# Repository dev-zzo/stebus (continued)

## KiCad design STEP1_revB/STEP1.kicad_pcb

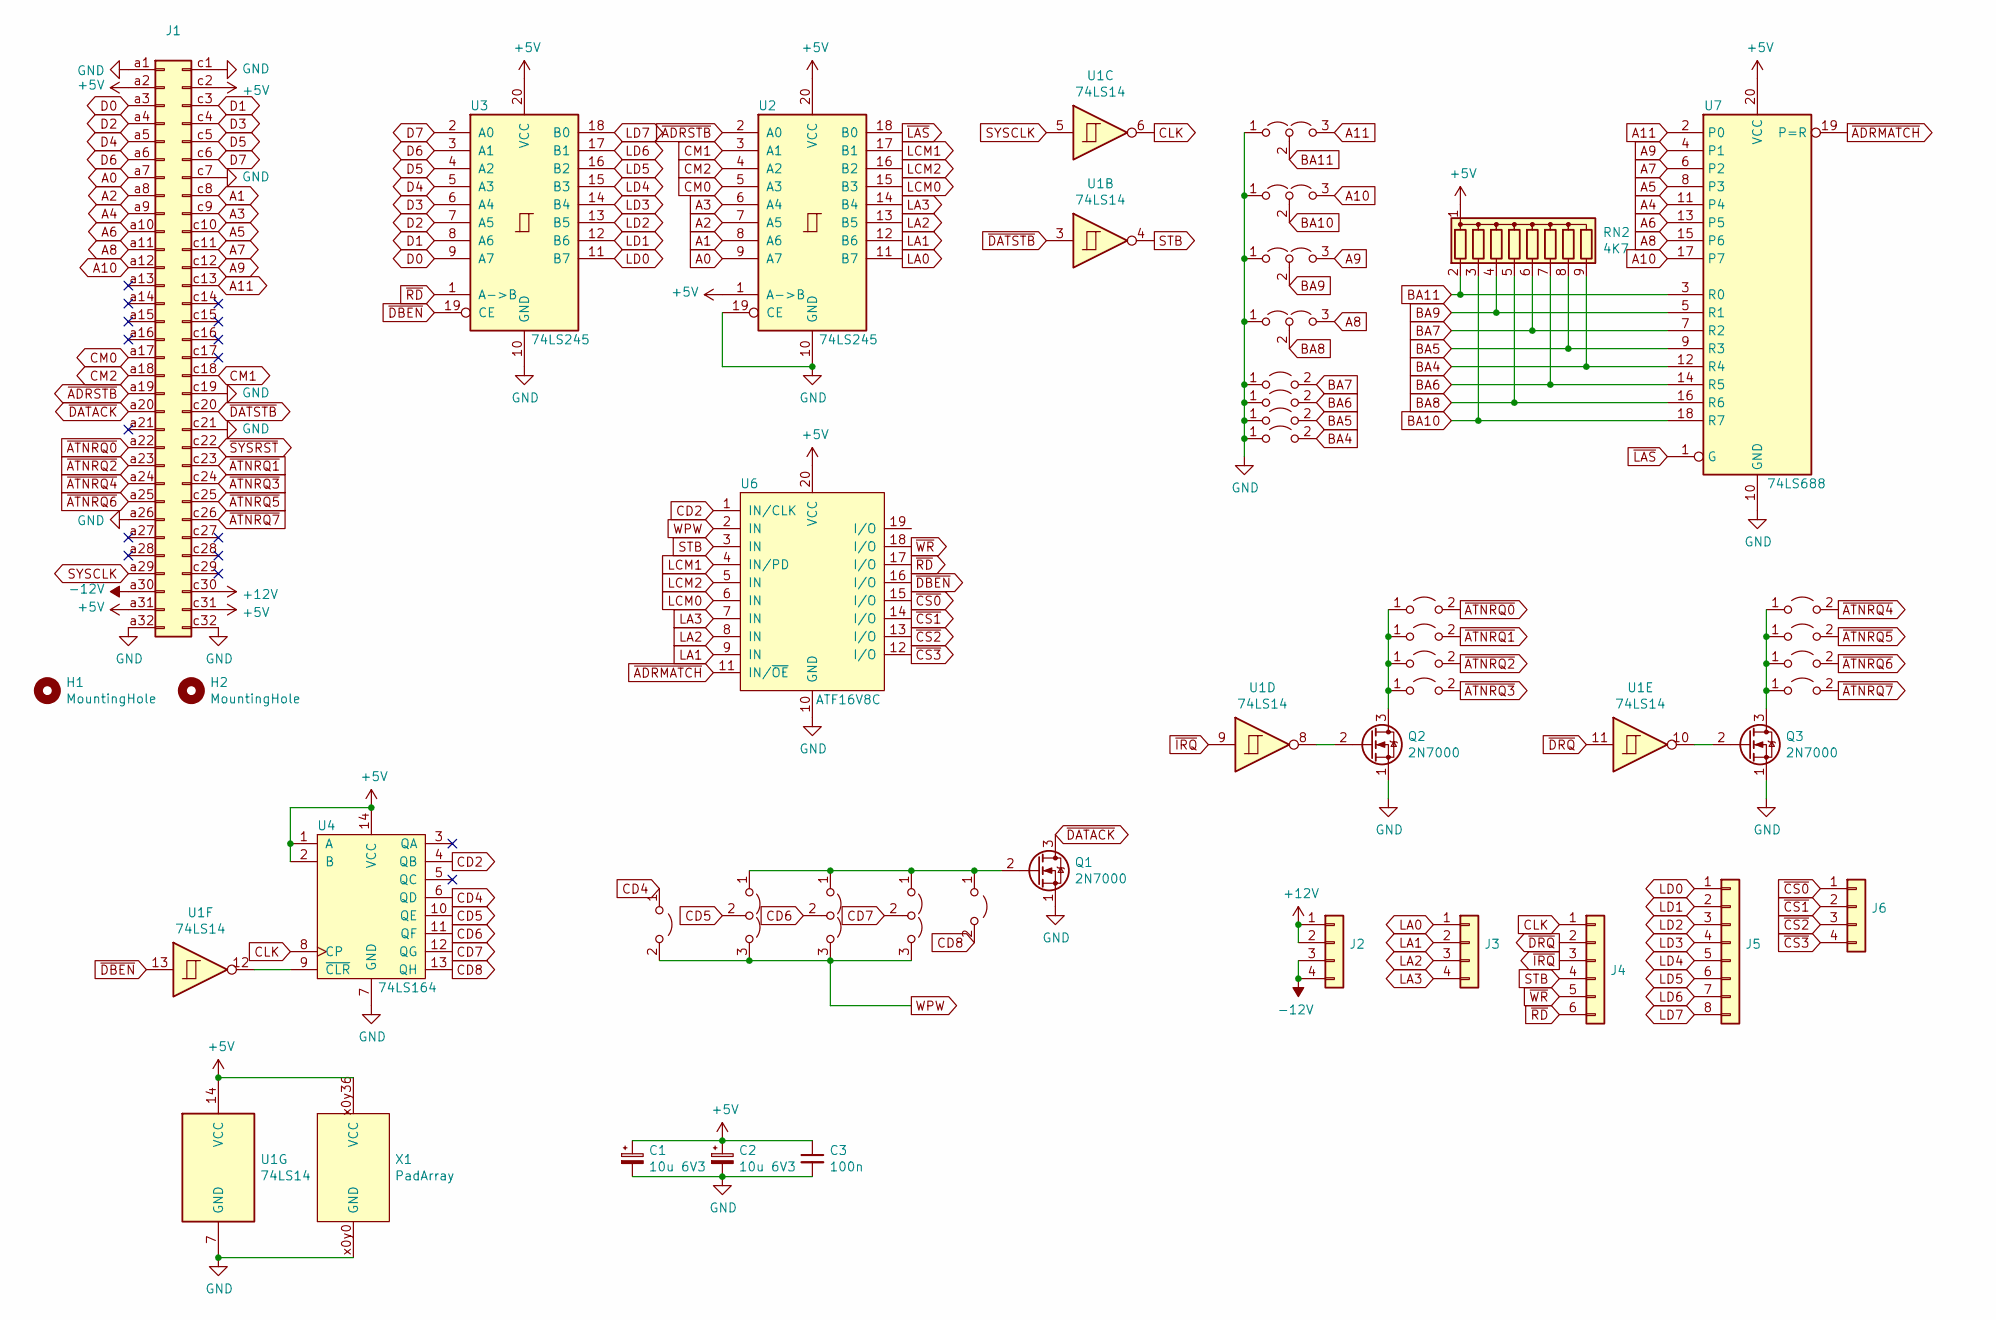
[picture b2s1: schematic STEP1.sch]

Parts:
C1, C2: 10u 6V3; CP_Radial_D5.0mm_P2.50mm
C3: 100n; C_Disc_D4.7mm_W2.5mm_P5.00mm
H1, H2: MountingHole; MountingHole_2.7mm_M2.5
J1: Connector_DIN41612_2x32; DIN41612_C_2x32_Male_Horizontal_THT
J2, J3, J6: Conn_01x04; PinHeader_1x04_P2.54mm_Vertical_No1
J4: Conn_01x06; PinHeader_1x06_P2.54mm_Vertical
J5: Conn_01x08; PinHeader_1x08_P2.54mm_Vertical_No1
JP1: 0; PinHeader_1x02_P2.54mm_Vertical_No1
JP2: 1; PinHeader_1x02_P2.54mm_Vertical_No1
JP3: 2; PinHeader_1x02_P2.54mm_Vertical_No1
JP4: 3; PinHeader_1x02_P2.54mm_Vertical_No1
JP5: 4; PinHeader_1x02_P2.54mm_Vertical_No1
JP6: 5; PinHeader_1x02_P2.54mm_Vertical_No1
JP7: 6; PinHeader_1x02_P2.54mm_Vertical_No1
JP8: 7; PinHeader_1x02_P2.54mm_Vertical_No1
JP9, JP14: E; PinHeader_1x02_P2.54mm_Vertical_No1
JP10, JP21: D; PinHeader_1x03_P2.54mm_Vertical_No1
JP11, JP20: C; PinHeader_1x03_P2.54mm_Vertical_No1
JP12, JP19: B; PinHeader_1x03_P2.54mm_Vertical_No1
JP13: A; PinHeader_1x02_P2.54mm_Vertical_No1
JP15: F; PinHeader_1x02_P2.54mm_Vertical_No1
JP16: G; PinHeader_1x02_P2.54mm_Vertical_No1
JP17: H; PinHeader_1x02_P2.54mm_Vertical_No1
JP18: A; PinHeader_1x03_P2.54mm_Vertical_No1
Q1, Q2, Q3: 2N7000; TO-92_Inline_Wide
RN2: 4K7; R_Array_SIP9
U1: 74LS14; DIP-14_W7.62mm
U2, U3: 74LS245; DIP-20_W7.62mm
U4: 74LS164; DIP-14_W7.62mm
U6: ATF16V8C; DIP-20_W7.62mm
U7: 74LS688; DIP-20_W7.62mm
X1: PadArray; Pad_Array

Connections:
+5V: C1.1, C2.1, C3.1, J1.a2, J1.a31, J1.c2, J1.c31, RN2.1 (common), U1.14 (VCC), U2.1 (A->B), U2.20 (VCC), U3.20 (VCC), U4.1 (A), U4.2 (B), U4.14 (VCC), U6.20 (VCC), U7.20 (VCC), X1.x0y36 (VCC), X1.x1y36 (VCC), X1.x2y36 (VCC), X1.x3y36 (VCC), X1.x4y36 (VCC), X1.x5y36 (VCC), X1.x6y36 (VCC), X1.x7y36 (VCC), X1.x8y36 (VCC), X1.x9y36 (VCC), X1.x10y36 (VCC), X1.x11y36 (VCC), X1.x12y36 (VCC), X1.x13y36 (VCC), X1.x14y36 (VCC), X1.x15y36 (VCC), X1.x16y36 (VCC), X1.x17y36 (VCC), X1.x18y36 (VCC), X1.x19y36 (VCC), X1.x20y36 (VCC), X1.x21y36 (VCC), X1.x22y36 (VCC), X1.x23y36 (VCC), X1.x24y36 (VCC), X1.x25y36 (VCC), X1.x26y36 (VCC), X1.x27y36 (VCC), X1.x28y36 (VCC), X1.x29y36 (VCC), X1.x30y36 (VCC), X1.x31y36 (VCC), X1.x32y36 (VCC), X1.x33y36 (VCC), X1.x34y36 (VCC), X1.x35y36 (VCC), X1.x36y36 (VCC), X1.x37y36 (VCC), X1.x38y36 (VCC), X1.x39y36 (VCC)
+12V: J1.c30, J2.1, J2.2
-12V: J1.a30, J2.3, J2.4
A0: J1.a7, U2.9 (A7)
A1: J1.c8, U2.8 (A6)
A2: J1.a8, U2.7 (A5)
A3: J1.c9, U2.6 (A4)
A4: J1.a9, U7.11 (P4)
A5: J1.c10, U7.8 (P3)
A6: J1.a10, U7.13 (P5)
A7: J1.c11, U7.6 (P2)
A8: J1.a11, JP21.3 (B), U7.15 (P6)
A9: J1.c12, JP20.3 (B), U7.4 (P1)
A10: J1.a12, JP19.3 (B), U7.17 (P7)
A11: J1.c13, JP18.3 (B), U7.2 (P0)
BA4: JP17.2 (B), RN2.9 (R8), U7.12 (R4)
BA5: JP16.2 (B), RN2.8 (R7), U7.9 (R3)
BA6: JP15.2 (B), RN2.7 (R6), U7.14 (R5)
BA7: JP14.2 (B), RN2.6 (R5), U7.7 (R2)
BA8: JP21.2 (C), RN2.5 (R4), U7.16 (R6)
BA9: JP20.2 (C), RN2.4 (R3), U7.5 (R1)
BA10: JP19.2 (C), RN2.3 (R2), U7.18 (R7)
BA11: JP18.2 (C), RN2.2 (R1), U7.3 (R0)
CD2: U4.4 (QB), U6.1 (IN/CLK)
CD4: JP9.1 (A), U4.6 (QD)
CD5: JP10.2 (C), U4.10 (QE)
CD6: JP11.2 (C), U4.11 (QF)
CD7: JP12.2 (C), U4.12 (QG)
CD8: JP13.2 (B), U4.13 (QH)
CLK: J4.1, U1.6, U4.8 (CP)
CM0: J1.a17, U2.5 (A3)
CM1: J1.c18, U2.3 (A1)
CM2: J1.a18, U2.4 (A2)
D0: J1.a3, U3.9 (A7)
D1: J1.c3, U3.8 (A6)
D2: J1.a4, U3.7 (A5)
D3: J1.c4, U3.6 (A4)
D4: J1.a5, U3.5 (A3)
D5: J1.c5, U3.4 (A2)
D6: J1.a6, U3.3 (A1)
D7: J1.c6, U3.2 (A0)
GND: C1.2, C2.2, C3.2, J1.a1, J1.a26, J1.a32, J1.c1, J1.c7, J1.c19, J1.c21, J1.c32, JP14.1 (A), JP15.1 (A), JP16.1 (A), JP17.1 (A), JP18.1 (A), JP19.1 (A), JP20.1 (A), JP21.1 (A), Q1.1 (S), Q2.1 (S), Q3.1 (S), U1.7 (GND), U2.10 (GND), U2.19 (CE), U3.10 (GND), U4.7 (GND), U6.10 (GND), U7.10 (GND), X1.x0y0 (GND), X1.x1y0 (GND), X1.x2y0 (GND), X1.x3y0 (GND), X1.x4y0 (GND), X1.x5y0 (GND), X1.x6y0 (GND), X1.x7y0 (GND), X1.x8y0 (GND), X1.x9y0 (GND), X1.x10y0 (GND), X1.x11y0 (GND), X1.x12y0 (GND), X1.x13y0 (GND), X1.x14y0 (GND), X1.x15y0 (GND), X1.x16y0 (GND), X1.x17y0 (GND), X1.x18y0 (GND), X1.x19y0 (GND), X1.x20y0 (GND), X1.x21y0 (GND), X1.x22y0 (GND), X1.x23y0 (GND), X1.x24y0 (GND), X1.x25y0 (GND), X1.x26y0 (GND), X1.x27y0 (GND), X1.x28y0 (GND), X1.x29y0 (GND), X1.x30y0 (GND), X1.x31y0 (GND), X1.x32y0 (GND), X1.x33y0 (GND), X1.x34y0 (GND), X1.x35y0 (GND), X1.x36y0 (GND), X1.x37y0 (GND), X1.x38y0 (GND), X1.x39y0 (GND)
LA0: J3.1, U2.11 (B7)
LA1: J3.2, U2.12 (B6), U6.9 (IN)
LA2: J3.3, U2.13 (B5), U6.8 (IN)
LA3: J3.4, U2.14 (B4), U6.7 (IN)
LCM0: U2.15 (B3), U6.6 (IN)
LCM1: U2.17 (B1), U6.4 (IN/PD)
LCM2: U2.16 (B2), U6.5 (IN)
LD0: J5.1, U3.11 (B7)
LD1: J5.2, U3.12 (B6)
LD2: J5.3, U3.13 (B5)
LD3: J5.4, U3.14 (B4)
LD4: J5.5, U3.15 (B3)
LD5: J5.6, U3.16 (B2)
LD6: J5.7, U3.17 (B1)
LD7: J5.8, U3.18 (B0)
unnamed: JP1.1 (A), JP2.1 (A), JP3.1 (A), JP4.1 (A), Q2.3 (D)
unnamed: JP5.1 (A), JP6.1 (A), JP7.1 (A), JP8.1 (A), Q3.3 (D)
unnamed: JP10.1 (A), JP11.1 (A), JP12.1 (A), JP13.1 (A), Q1.2 (G)
unnamed: Q2.2 (G), U1.8
unnamed: Q3.2 (G), U1.10
unnamed: U1.12, U4.9 (~CLR)
STB: J4.4, U1.4, U6.3 (IN)
SYSCLK: J1.a29, U1.5
WPW: JP9.2 (B), JP10.3 (B), JP11.3 (B), JP12.3 (B), U6.2 (IN)
~ADRMATCH: U6.11 (IN/~OE), U7.19 (P=R)
~ADRSTB: J1.a19, U2.2 (A0)
~ATNRQ0: J1.a22, JP1.2 (B)
~ATNRQ1: J1.c23, JP2.2 (B)
~ATNRQ2: J1.a23, JP3.2 (B)
~ATNRQ3: J1.c24, JP4.2 (B)
~ATNRQ4: J1.a24, JP5.2 (B)
~ATNRQ5: J1.c25, JP6.2 (B)
~ATNRQ6: J1.a25, JP7.2 (B)
~ATNRQ7: J1.c26, JP8.2 (B)
~CS0: J6.1, U6.15 (I/O)
~CS1: J6.2, U6.14 (I/O)
~CS2: J6.3, U6.13 (I/O)
~CS3: J6.4, U6.12 (I/O)
~DATACK: J1.a20, Q1.3 (D)
~DATSTB: J1.c20, U1.3
~DBEN: U1.13, U3.19 (CE), U6.16 (I/O)
~DRQ: J4.2, U1.11
~IRQ: J4.3, U1.9
~LAS: U2.18 (B0), U7.1 (G)
~RD: J4.6, U3.1 (A->B), U6.17 (I/O)
~WR: J4.5, U6.18 (I/O)

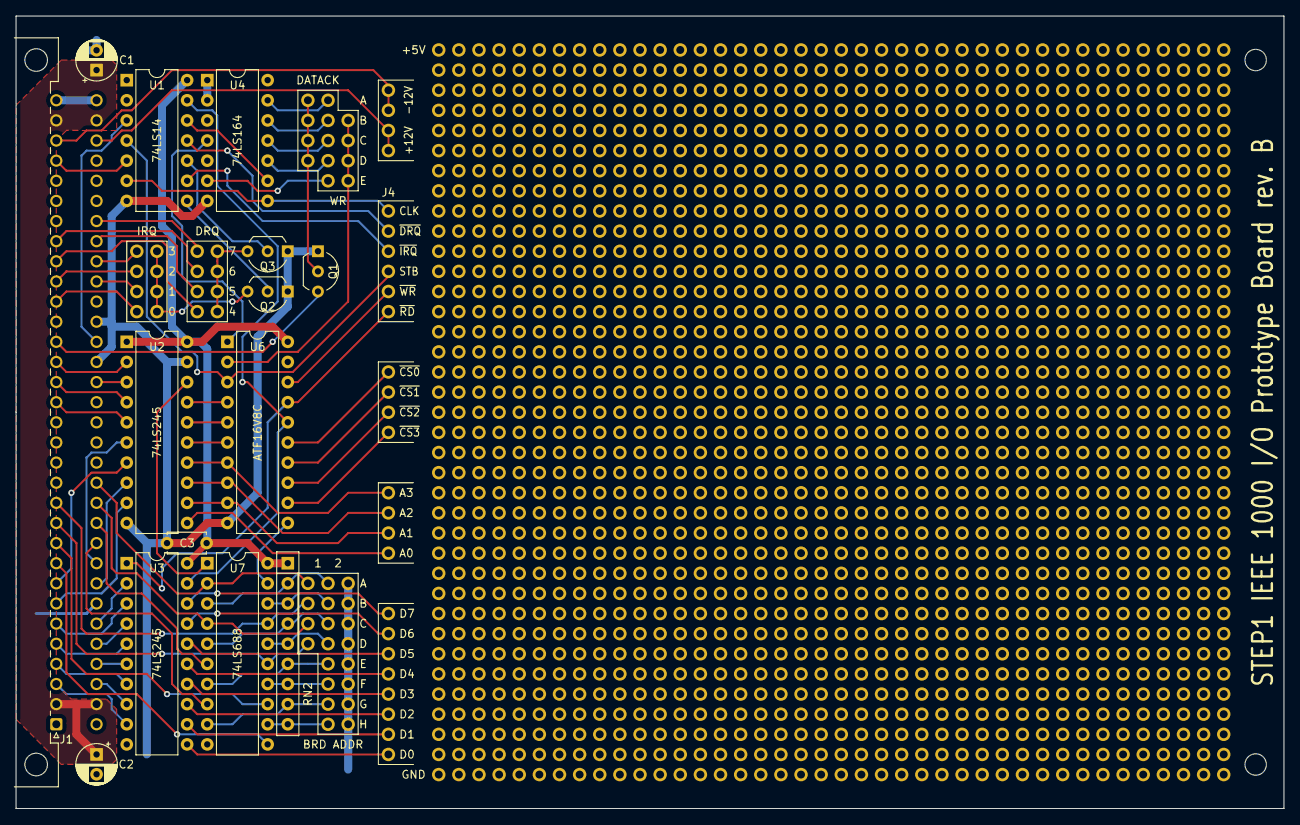
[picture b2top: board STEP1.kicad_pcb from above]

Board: 2 copper layers, 160.0 x 100.0 mm, 43 parts (0 on the bottom side), 88 nets.

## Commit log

2021-01-19 adding gitignore
2021-01-19 adding project-wide symbol lib
2021-01-19 adding S68k8 and STEP1
2021-01-23 S68k8: add docs for reference
2021-01-23 Update gitignore
2021-01-23 S68k8: change pull-up for DTACK to a separate resistor
    Tests show 4k7 is too large to pull the line back fast enough. Reducing to 1k or even 470R give much better results.
2021-01-23 More docs!
2021-01-23 S68k8: moved copper pours for power distribution to the bottom layer
